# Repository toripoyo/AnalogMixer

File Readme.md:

# About

3Ch Analog Mixer with bluetooth in/out.

## Input

- Line in 1  
- Line in 2 / Bluetooth in (Selectable)  
- Mic in  

## Output

- Monitor out (headphone)
- Line out
- Bluetooth out (Mix/Mic Selectable)

## Power

- Micro USB

## Other

- Peak warning LED (-10dBV)

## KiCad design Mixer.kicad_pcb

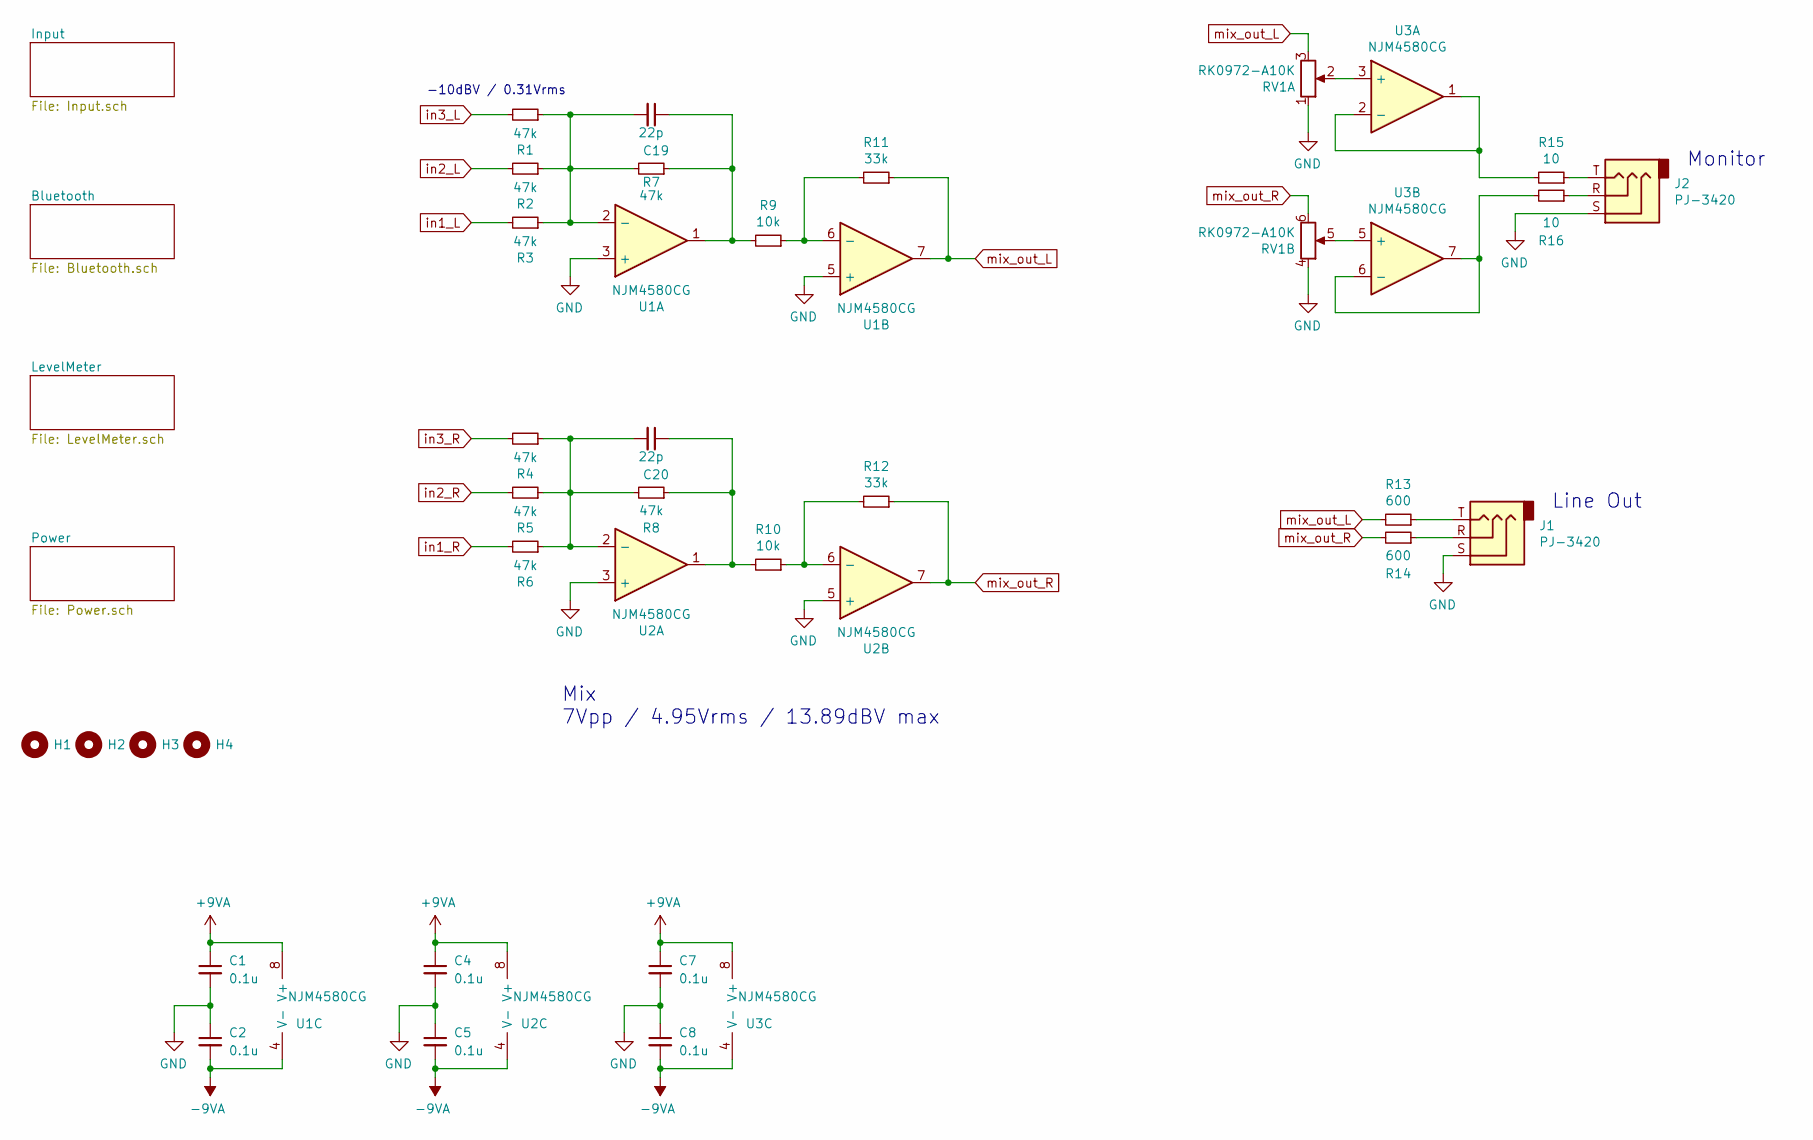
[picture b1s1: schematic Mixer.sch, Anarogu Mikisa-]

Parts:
C1, C2, C4, C5, C7, C8: 0.1u; C_0603_1608Metric_Pad1.05x0.95mm_HandSolder
C19, C20: 22p; C_0603_1608Metric_Pad1.05x0.95mm_HandSolder
H1, H2, H3, H4: MountingHole; MountingHole_3.2mm_M3
J1, J2: PJ-3420
R1, R2, R3, R4, R5, R6, R7, R8: 47k; R_0603_1608Metric_Pad1.05x0.95mm_HandSolder
R9, R10: 10k; R_0603_1608Metric_Pad1.05x0.95mm_HandSolder
R11, R12: 33k; R_0603_1608Metric_Pad1.05x0.95mm_HandSolder
R13, R14: 600; R_0603_1608Metric_Pad1.05x0.95mm_HandSolder
R15, R16: 10; R_0603_1608Metric_Pad1.05x0.95mm_HandSolder
RV1: RK0972-A10K; RD925G-QA1
U1, U2, U3: NJM4580CG; SOP-8_3.9x4.9mm_P1.27mm

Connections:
+9VA: C1.1, C4.1, C7.1, U1.8 (V+), U2.8 (V+), U3.8 (V+); also elsewhere on the board
-9VA: C2.2, C5.2, C8.2, U1.4 (V-), U2.4 (V-), U3.4 (V-); also elsewhere on the board
GND: C1.2, C2.1, C4.2, C5.1, C7.2, C8.1, J1.S, J2.S, RV1.1, RV1.4, U1.3 (+), U1.5 (+), U2.3 (+), U2.5 (+); also elsewhere on the board
unnamed: C19.1, R7.1, R9.2, U1.1
unnamed: C19.2, R1.1, R2.1, R3.1, R7.2, U1.2 (-)
unnamed: C20.1, R8.1, R10.2, U2.1
unnamed: C20.2, R4.1, R5.1, R6.1, R8.2, U2.2 (-)
unnamed: J1.R, R14.1
unnamed: J1.T, R13.1
unnamed: J2.R, R16.1
unnamed: J2.T, R15.1
unnamed: R10.1, R12.2, U2.6 (-)
unnamed: R9.1, R11.2, U1.6 (-)
unnamed: R15.2, U3.1, U3.2 (-)
unnamed: R16.2, U3.6 (-), U3.7
unnamed: RV1.2, U3.3 (+)
unnamed: RV1.5, U3.5 (+)
in1_L: R3.2; also elsewhere on the board
in1_R: R6.2; also elsewhere on the board
in2_L: R2.2; also elsewhere on the board
in2_R: R5.2; also elsewhere on the board
in3_L: R1.2; also elsewhere on the board
in3_R: R4.2; also elsewhere on the board
mix_out_L: R11.1, R13.2, RV1.3, U1.7; also elsewhere on the board
mix_out_R: R12.1, R14.2, RV1.6, U2.7; also elsewhere on the board

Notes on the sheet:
-10dBV / 0.31Vrms
Monitor
Line Out
Mix 7Vpp / 4.95Vrms / 13.89dBV max

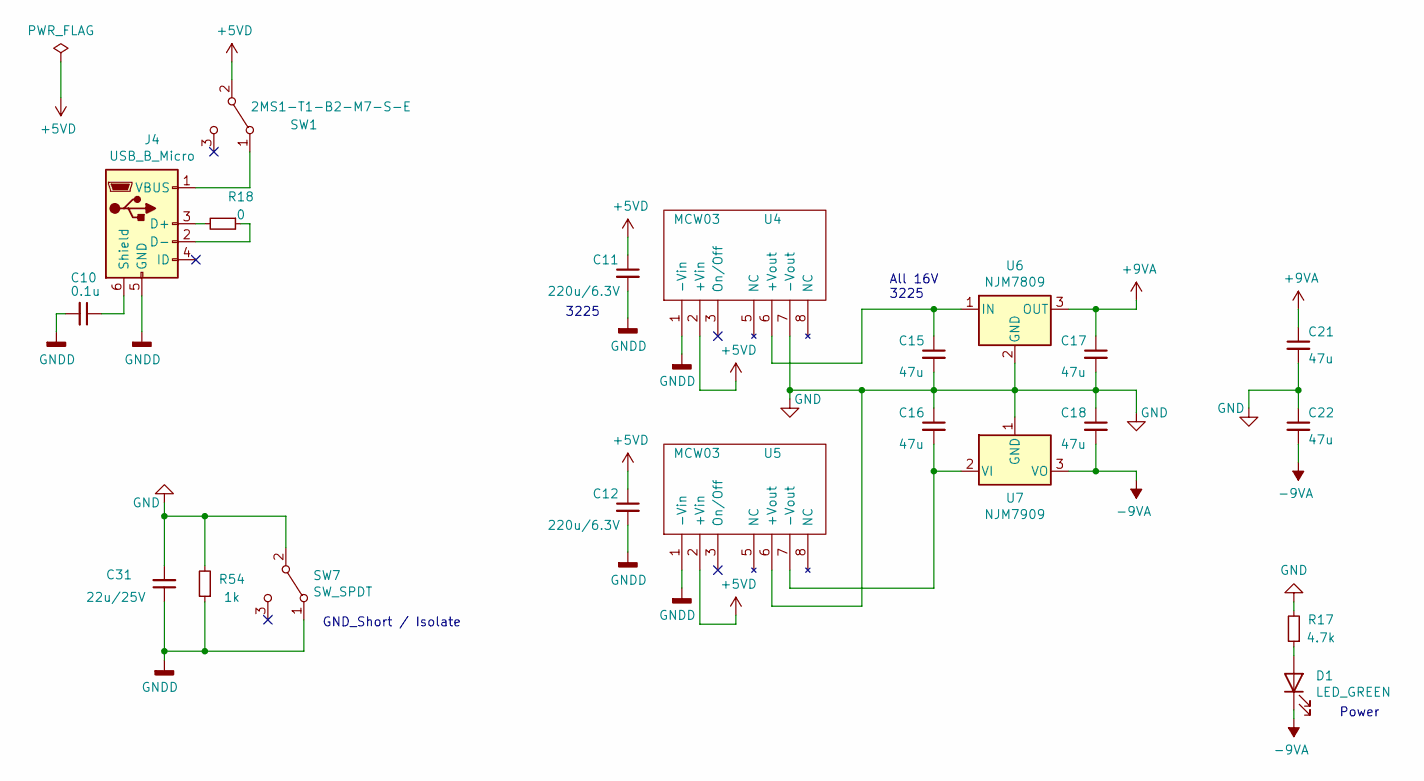
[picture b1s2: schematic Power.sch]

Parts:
C10: 0.1u; C_0603_1608Metric_Pad1.05x0.95mm_HandSolder
C11, C12: 220u/6.3V; C_1210_3225Metric_Pad1.42x2.65mm_HandSolder
C15, C16, C17, C18, C21, C22: 47u; C_1210_3225Metric_Pad1.42x2.65mm_HandSolder
C31: 22u/25V; C_0805_2012Metric_Pad1.15x1.40mm_HandSolder
D1: LED_GREEN; LED_0603_1608Metric_Pad1.05x0.95mm_HandSolder
J4: USB_B_Micro; USB_Micro_B_Female_10118193-0001LF
R17: 4.7k; R_0603_1608Metric_Pad1.05x0.95mm_HandSolder
R18: 0; R_0603_1608Metric_Pad1.05x0.95mm_HandSolder
R54: 1k; R_0603_1608Metric_Pad1.05x0.95mm_HandSolder
SW1: 2MS1-T1-B2-M7-S-E; T1-B2-M7-S-E
SW7: SW_SPDT; SW_Slide_1P2T_CK_OS102011MS2Q
U4, U5: MCW03
U6: NJM7809; TO-220-3_Vertical
U7: NJM7909; TO-220-3_Vertical

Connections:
+5VD: C11.1, C12.1, SW1.2 (B), U4.2 (+Vin), U5.2 (+Vin); also elsewhere on the board
+9VA: C17.1, C21.1, U6.3 (OUT); also elsewhere on the board
-9VA: C18.2, C22.2, D1.1 (K), U7.3 (VO); also elsewhere on the board
GND: C15.2, C16.1, C17.2, C18.1, C21.2, C22.1, C31.2, R17.2, R54.2, SW7.2 (B), U4.7 (-Vout), U5.6 (+Vout), U6.2 (GND), U7.1 (GND); also elsewhere on the board
GNDD: C10.2, C11.2, C12.2, C31.1, J4.5 (GND), R54.1, SW7.1 (A), U4.1 (-Vin), U5.1 (-Vin); also elsewhere on the board
unnamed: C10.1, J4.6 (Shield)
unnamed: C15.1, U4.6 (+Vout), U6.1 (IN)
unnamed: C16.2, U5.7 (-Vout), U7.2 (VI)
unnamed: D1.2 (A), R17.1
unnamed: J4.1 (VBUS), SW1.1 (A)
unnamed: J4.2 (D-), R18.1
unnamed: J4.3 (D+), R18.2

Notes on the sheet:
All 16V 3225
3225
Power
GND_Short / Isolate

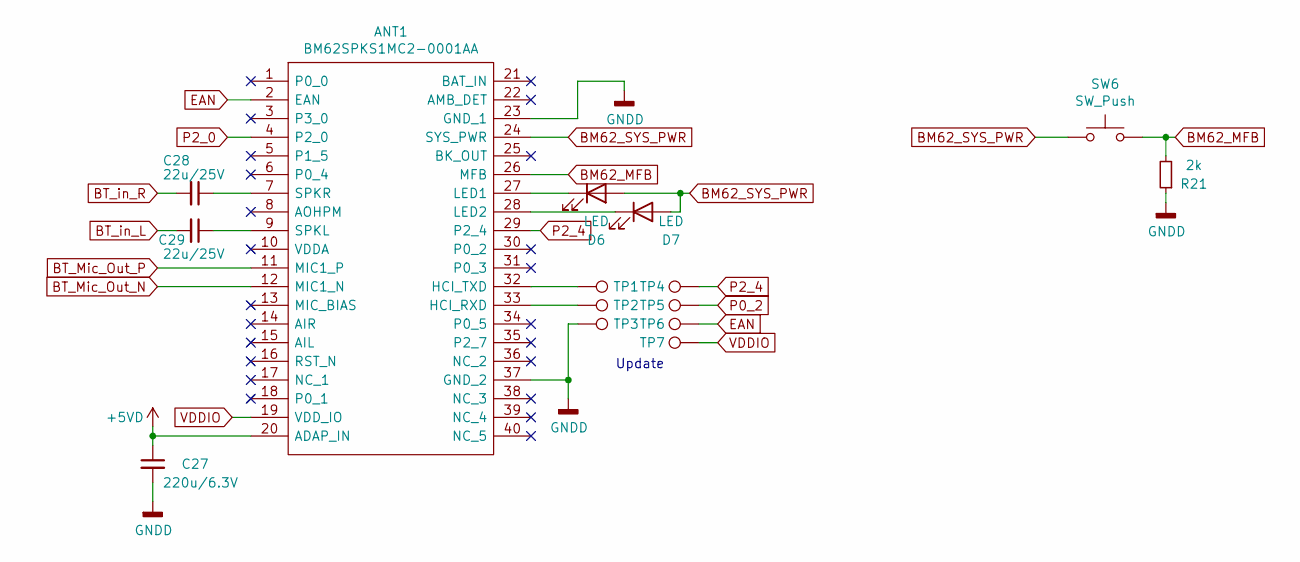
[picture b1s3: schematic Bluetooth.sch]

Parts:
ANT1: BM62SPKS1MC2-0001AA; BM62; Manufacturer_Part_Number BM62SPKS1MC2-0001AA; Mouser Part Number 579-62SPKS1MC20001AA
C27: 220u/6.3V; C_1210_3225Metric_Pad1.42x2.65mm_HandSolder
C28, C29: 22u/25V; C_0805_2012Metric_Pad1.15x1.40mm_HandSolder
D6, D7: LED; LED_0603_1608Metric_Pad1.05x0.95mm_HandSolder
R21: 2k; R_0603_1608Metric_Pad1.05x0.95mm_HandSolder
SW6: SW_Push; SW_PUSH_6mm
TP1, TP2, TP3, TP4, TP5, TP6, TP7: TestPoint; TestPoint_Pad_D1.0mm

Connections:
+5VD: ANT1.20 (ADAP_IN), C27.1; also elsewhere on the board
BM62_MFB: ANT1.26 (MFB), R21.2, SW6.2
BM62_SYS_PWR: ANT1.24 (SYS_PWR), D6.2 (A), D7.2 (A), SW6.1
BT_Mic_Out_N: ANT1.12 (MIC1_N); also elsewhere on the board
BT_Mic_Out_P: ANT1.11 (MIC1_P); also elsewhere on the board
BT_in_L: C29.2; also elsewhere on the board
BT_in_R: C28.2; also elsewhere on the board
EAN: ANT1.2 (EAN), TP6.1
GNDD: ANT1.23 (GND_1), ANT1.37 (GND_2), C27.2, R21.1, TP3.1; also elsewhere on the board
unnamed: ANT1.7 (SPKR), C28.1
unnamed: ANT1.9 (SPKL), C29.1
unnamed: ANT1.27 (LED1), D6.1 (K)
unnamed: ANT1.28 (LED2), D7.1 (K)
unnamed: ANT1.32 (HCI_TXD), TP1.1
unnamed: ANT1.33 (HCI_RXD), TP2.1
P2_4: ANT1.29 (P2_4), TP4.1
VDDIO: ANT1.19 (VDD_IO), TP7.1

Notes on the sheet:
Update

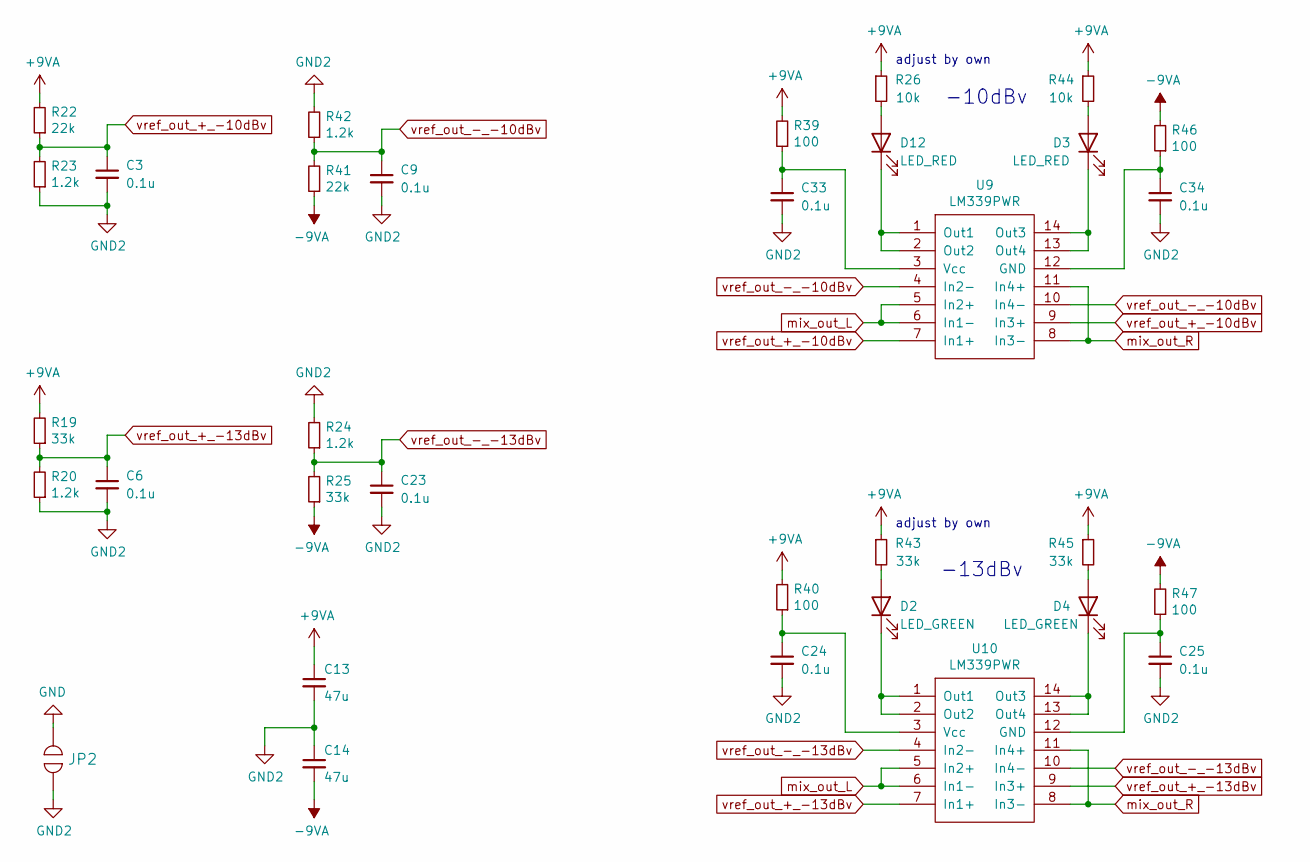
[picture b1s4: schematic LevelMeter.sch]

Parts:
C3, C6, C9, C23, C24, C25, C33, C34: 0.1u; C_0603_1608Metric_Pad1.05x0.95mm_HandSolder
C13, C14: 47u; C_1210_3225Metric_Pad1.42x2.65mm_HandSolder
D2, D4: LED_GREEN; LED_0603_1608Metric_Pad1.05x0.95mm_HandSolder
D3, D12: LED_RED; LED_0603_1608Metric_Pad1.05x0.95mm_HandSolder
JP2: UserShort; SolderJumper-2_P1.3mm_Open_RoundedPad1.0x1.5mm
R19, R25, R43, R45: 33k; R_0603_1608Metric_Pad1.05x0.95mm_HandSolder
R20, R23, R24, R42: 1.2k; R_0603_1608Metric_Pad1.05x0.95mm_HandSolder
R22, R41: 22k; R_0603_1608Metric_Pad1.05x0.95mm_HandSolder
R26, R44: 10k; R_0603_1608Metric_Pad1.05x0.95mm_HandSolder
R39, R40, R46, R47: 100; R_0603_1608Metric_Pad1.05x0.95mm_HandSolder
U9, U10: LM339PWR; TSSOP-14_4.4x5mm_P0.65mm

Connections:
+9VA: C13.1, R19.2, R22.2, R26.1, R39.2, R40.2, R43.1, R44.1, R45.1; also elsewhere on the board
-9VA: C14.2, R25.1, R41.1, R46.2, R47.2; also elsewhere on the board
GND: JP2.1; also elsewhere on the board
GND2: C3.2, C6.2, C9.2, C13.2, C14.1, C23.2, C24.2, C25.2, C33.2, C34.2, JP2.2, R20.1, R23.1, R24.2, R42.2
unnamed: C24.1, R40.1, U10.3 (Vcc)
unnamed: C25.1, R47.1, U10.12 (GND)
unnamed: C33.1, R39.1, U9.3 (Vcc)
unnamed: C34.1, R46.1, U9.12 (GND)
unnamed: D2.1 (K), U10.1 (Out1), U10.2 (Out2)
unnamed: D2.2 (A), R43.2
unnamed: D3.1 (K), U9.13 (Out4), U9.14 (Out3)
unnamed: D3.2 (A), R44.2
unnamed: D4.1 (K), U10.13 (Out4), U10.14 (Out3)
unnamed: D4.2 (A), R45.2
unnamed: D12.1 (K), U9.1 (Out1), U9.2 (Out2)
unnamed: D12.2 (A), R26.2
mix_out_L: U9.5 (In2+), U9.6 (In1-), U10.5 (In2+), U10.6 (In1-); also elsewhere on the board
mix_out_R: U9.8 (In3-), U9.11 (In4+), U10.8 (In3-), U10.11 (In4+); also elsewhere on the board
vref_out_+_-10dBv: C3.1, R22.1, R23.2, U9.7 (In1+), U9.9 (In3+)
vref_out_+_-13dBv: C6.1, R19.1, R20.2, U10.7 (In1+), U10.9 (In3+)
vref_out_-_-10dBv: C9.1, R41.2, R42.1, U9.4 (In2-), U9.10 (In4-)
vref_out_-_-13dBv: C23.1, R24.1, R25.2, U10.4 (In2-), U10.10 (In4-)

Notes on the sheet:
-10dBv
-13dBv
adjust by own

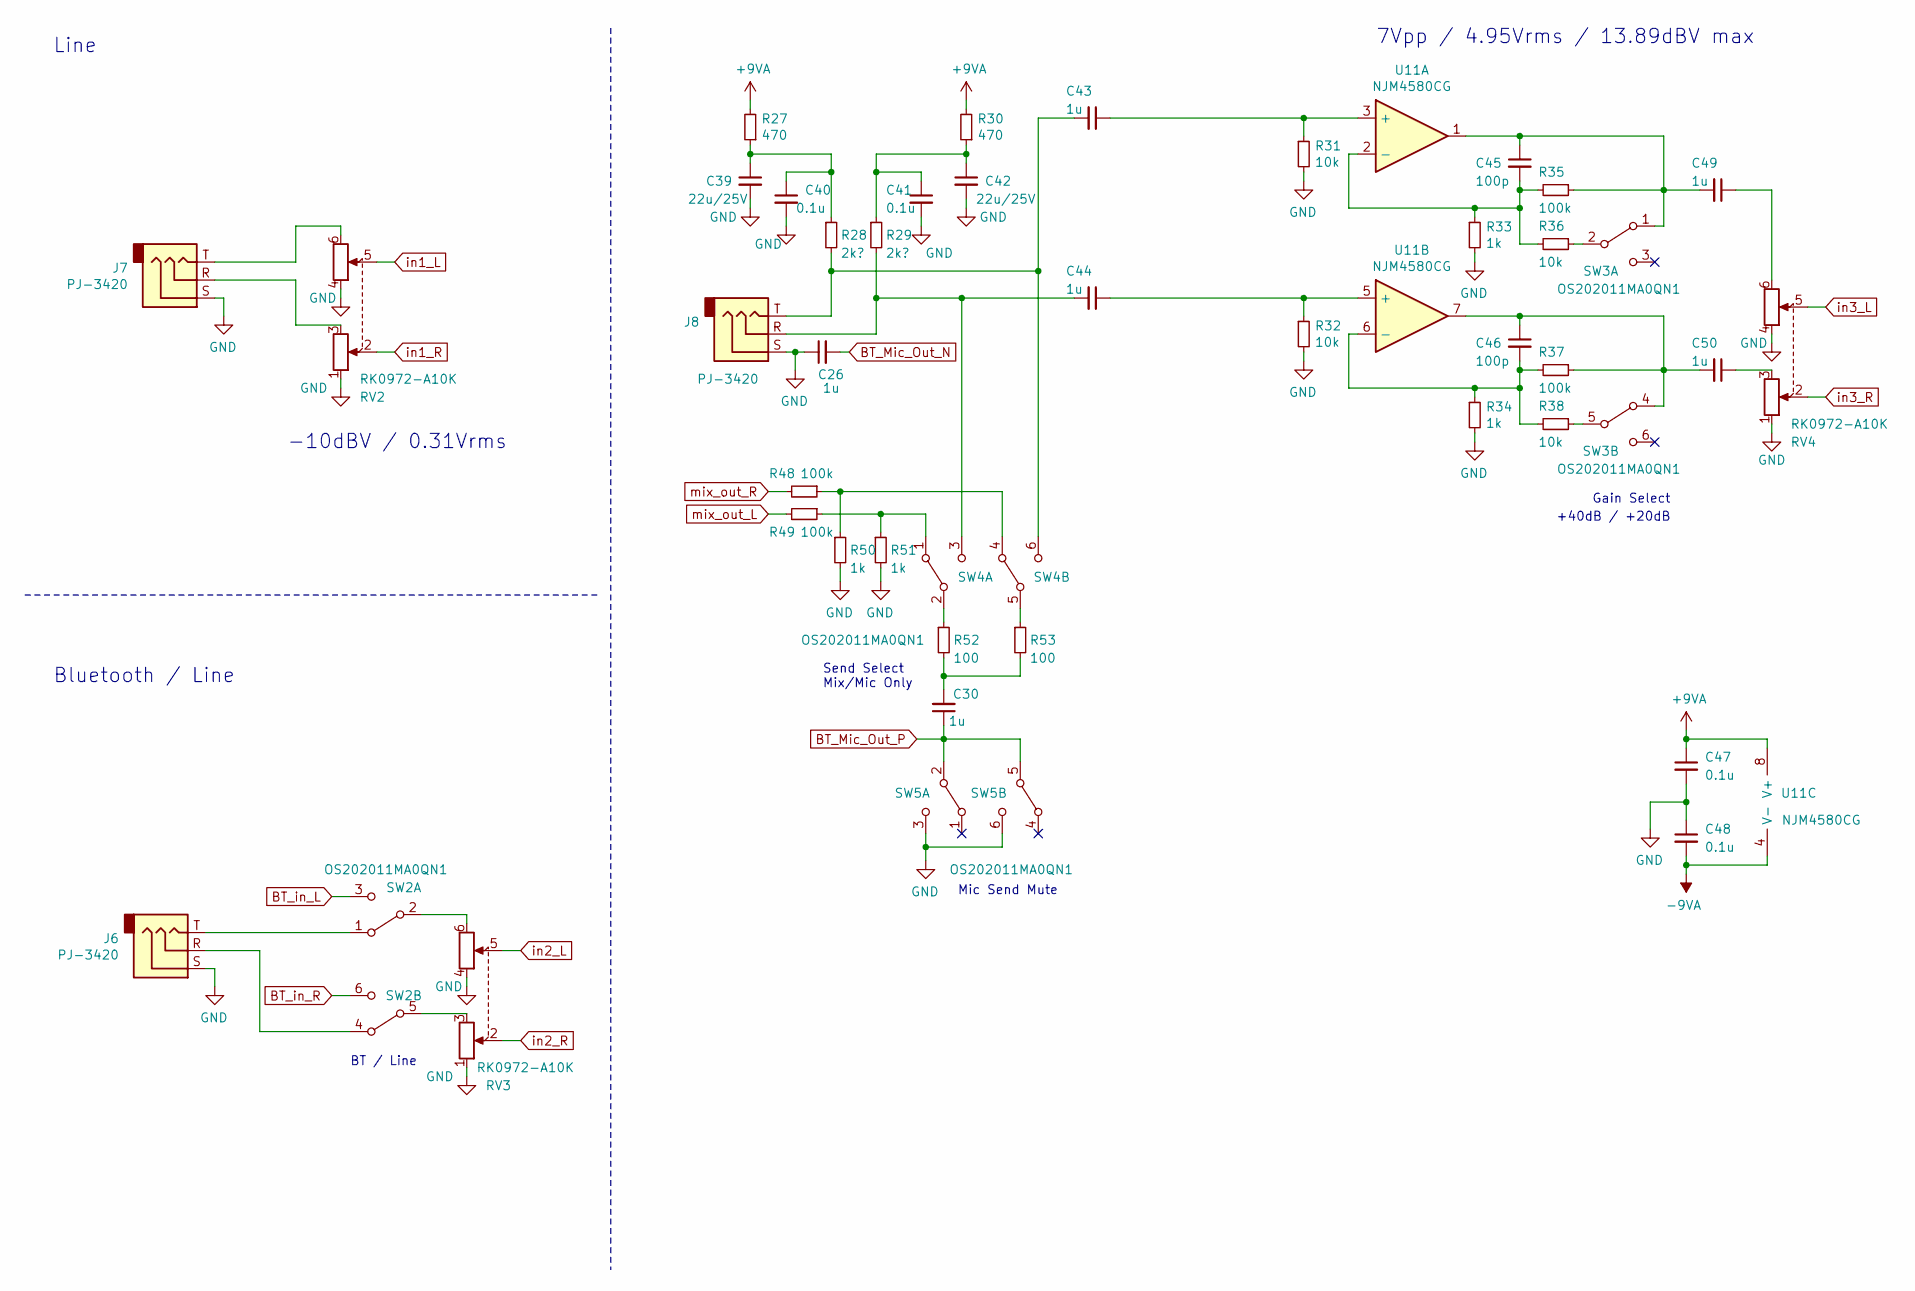
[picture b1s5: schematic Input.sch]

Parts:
C26, C30, C43, C44, C49, C50: 1u; C_0603_1608Metric_Pad1.05x0.95mm_HandSolder
C39, C42: 22u/25V; C_0805_2012Metric_Pad1.15x1.40mm_HandSolder
C40, C41, C47, C48: 0.1u; C_0603_1608Metric_Pad1.05x0.95mm_HandSolder
C45, C46: 100p; C_0603_1608Metric_Pad1.05x0.95mm_HandSolder
J6, J7, J8: PJ-3420
R27, R30: 470; R_0603_1608Metric_Pad1.05x0.95mm_HandSolder
R28, R29: 2k?; R_0603_1608Metric_Pad1.05x0.95mm_HandSolder
R31, R32, R36, R38: 10k; R_0603_1608Metric_Pad1.05x0.95mm_HandSolder
R33, R34, R50, R51: 1k; R_0603_1608Metric_Pad1.05x0.95mm_HandSolder
R35, R37, R48, R49: 100k; R_0603_1608Metric_Pad1.05x0.95mm_HandSolder
R52, R53: 100; R_0603_1608Metric_Pad1.05x0.95mm_HandSolder
RV2, RV3, RV4: RK0972-A10K; RD925G-QA1
SW2, SW3, SW4, SW5: OS202011MA0QN1
U11: NJM4580CG; SOP-8_3.9x4.9mm_P1.27mm

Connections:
+9VA: C47.1, R27.2, R30.2, U11.8 (V+); also elsewhere on the board
-9VA: C48.2, U11.4 (V-); also elsewhere on the board
BT_Mic_Out_N: C26.2; also elsewhere on the board
BT_Mic_Out_P: C30.1, SW5.2 (B), SW5.5 (B); also elsewhere on the board
BT_in_L: SW2.3 (C); also elsewhere on the board
BT_in_R: SW2.6 (C); also elsewhere on the board
GND: C26.1, C39.2, C40.2, C41.2, C42.2, C47.2, C48.1, J6.S, J7.S, J8.S, R31.2, R32.2, R33.2, R34.2, R50.2, R51.2, RV2.1, RV2.4, RV3.1, RV3.4, RV4.1, RV4.4, SW5.3 (C), SW5.6 (C); also elsewhere on the board
unnamed: C30.2, R52.2, R53.2
unnamed: C39.1, C40.1, R27.1, R28.1
unnamed: C41.1, C42.1, R29.1, R30.1
unnamed: C43.1, R31.1, U11.3 (+)
unnamed: C43.2, J8.T, R28.2, SW4.6 (C)
unnamed: C44.1, R32.1, U11.5 (+)
unnamed: C44.2, J8.R, R29.2, SW4.3 (C)
unnamed: C45.1, C49.2, R35.1, SW3.1 (A), U11.1
unnamed: C45.2, R33.1, R35.2, R36.2, U11.2 (-)
unnamed: C46.1, C50.2, R37.1, SW3.4 (A), U11.7
unnamed: C46.2, R34.1, R37.2, R38.2, U11.6 (-)
unnamed: C49.1, RV4.6
unnamed: C50.1, RV4.3
unnamed: J6.R, SW2.4 (A)
unnamed: J6.T, SW2.1 (A)
unnamed: J7.R, RV2.3
unnamed: J7.T, RV2.6
unnamed: R36.1, SW3.2 (B)
unnamed: R38.1, SW3.5 (B)
unnamed: R48.1, R50.1, SW4.4 (A)
unnamed: R49.1, R51.1, SW4.1 (A)
unnamed: R52.1, SW4.2 (B)
unnamed: R53.1, SW4.5 (B)
unnamed: RV3.3, SW2.5 (B)
unnamed: RV3.6, SW2.2 (B)
in1_L: RV2.5; also elsewhere on the board
in1_R: RV2.2; also elsewhere on the board
in2_L: RV3.5; also elsewhere on the board
in2_R: RV3.2; also elsewhere on the board
in3_L: RV4.5; also elsewhere on the board
in3_R: RV4.2; also elsewhere on the board
mix_out_L: R49.2; also elsewhere on the board
mix_out_R: R48.2; also elsewhere on the board

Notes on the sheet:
+40dB / +20dB
-10dBV / 0.31Vrms
7Vpp / 4.95Vrms / 13.89dBV max
Bluetooth / Line
BT / Line
Line
Gain Select
Send Select Mix/Mic Only
Mic Send Mute

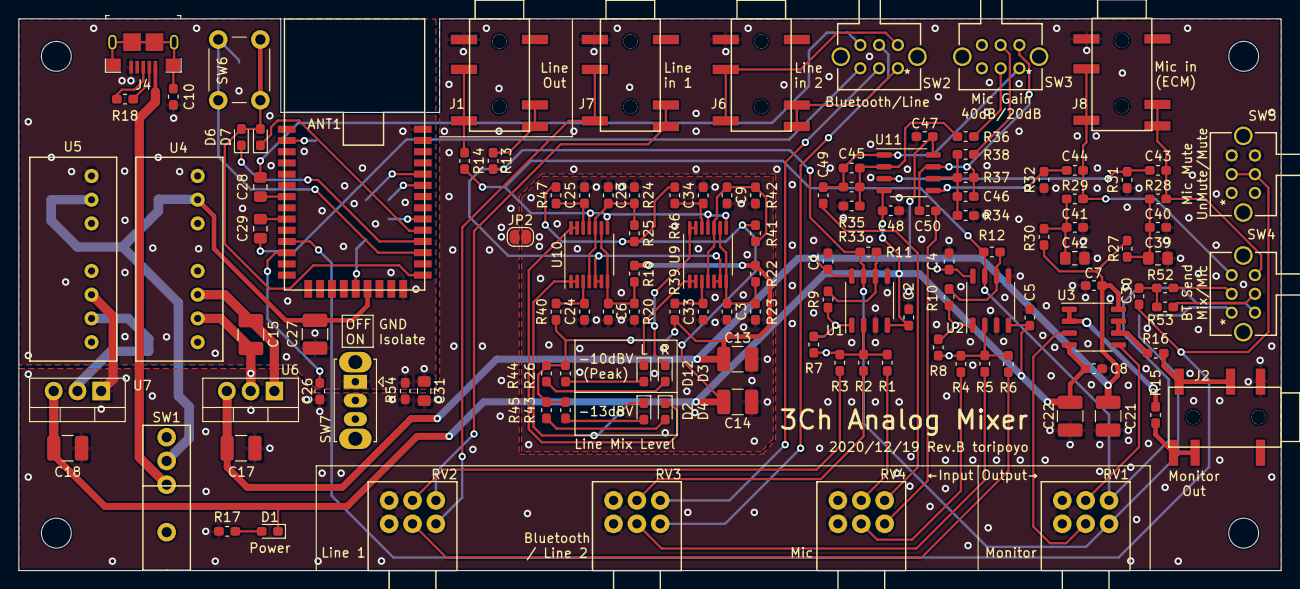
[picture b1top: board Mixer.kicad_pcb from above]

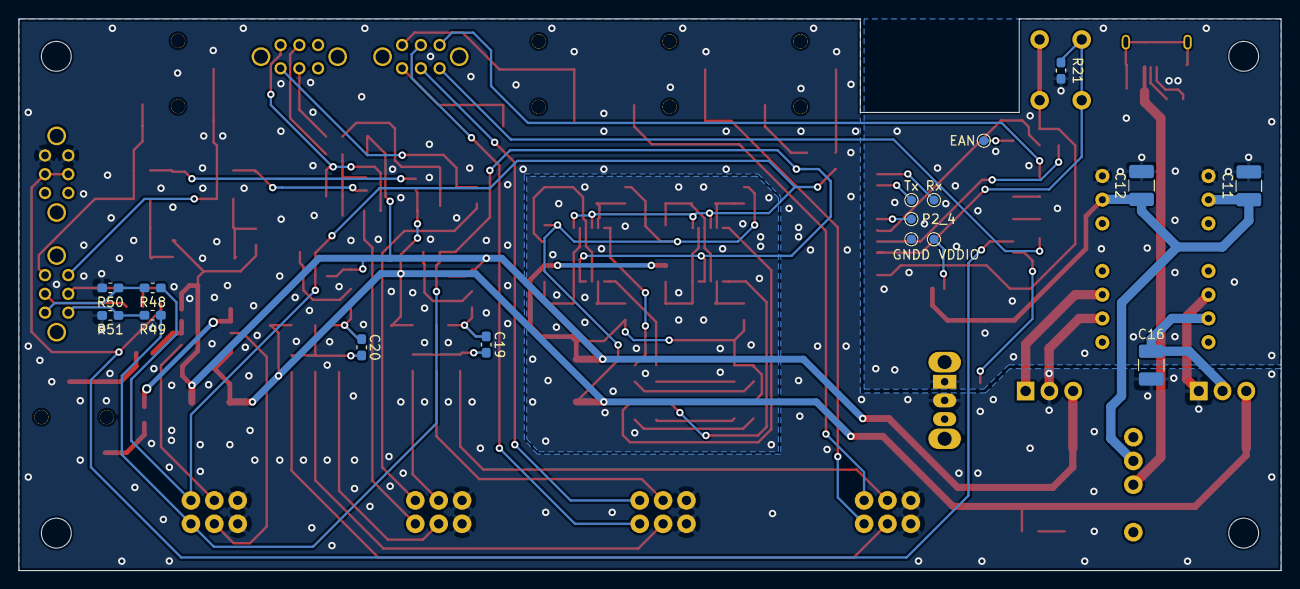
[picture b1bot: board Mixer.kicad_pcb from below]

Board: 2 copper layers, 135.0 x 59.0 mm, 145 parts (16 on the bottom side), 91 nets.

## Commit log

2020-07-24 Add Readme and schematic pdf.
2020-08-24 Rev.A 作成中
2020-11-24 Rev.A 完成
2020-11-24 Add B.Cu gbr
2020-11-24 Add Schematic pdf
2020-11-24 Fix Gerber Bug
2020-12-19 Rev.B 改版完了
2020-12-19 シルク修正

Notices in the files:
parts and their libraries:
Copyright 2016 Accelerated Designs. All rights reserved.
